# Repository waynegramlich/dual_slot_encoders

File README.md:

# dual_slot_encoders

Quadrature encoder using two slot photointerrupters

## Revision A Issues

* The footprint holes for the slot encoders are too small. [x]

## Revision B Issues

* Use a 2x4 ribbon cable for both encoder signals and motor power.

## Revision D Issues

* Pins 4/5 and 6/7 are swapped in bus_bridge_encoders_sonar (Rev. C)
  and dual_slot_encoders (Rev. D). [Swapped 4/5 and 6/7.]

## Revision E Issuses

* Both resistors are too close to the edge.

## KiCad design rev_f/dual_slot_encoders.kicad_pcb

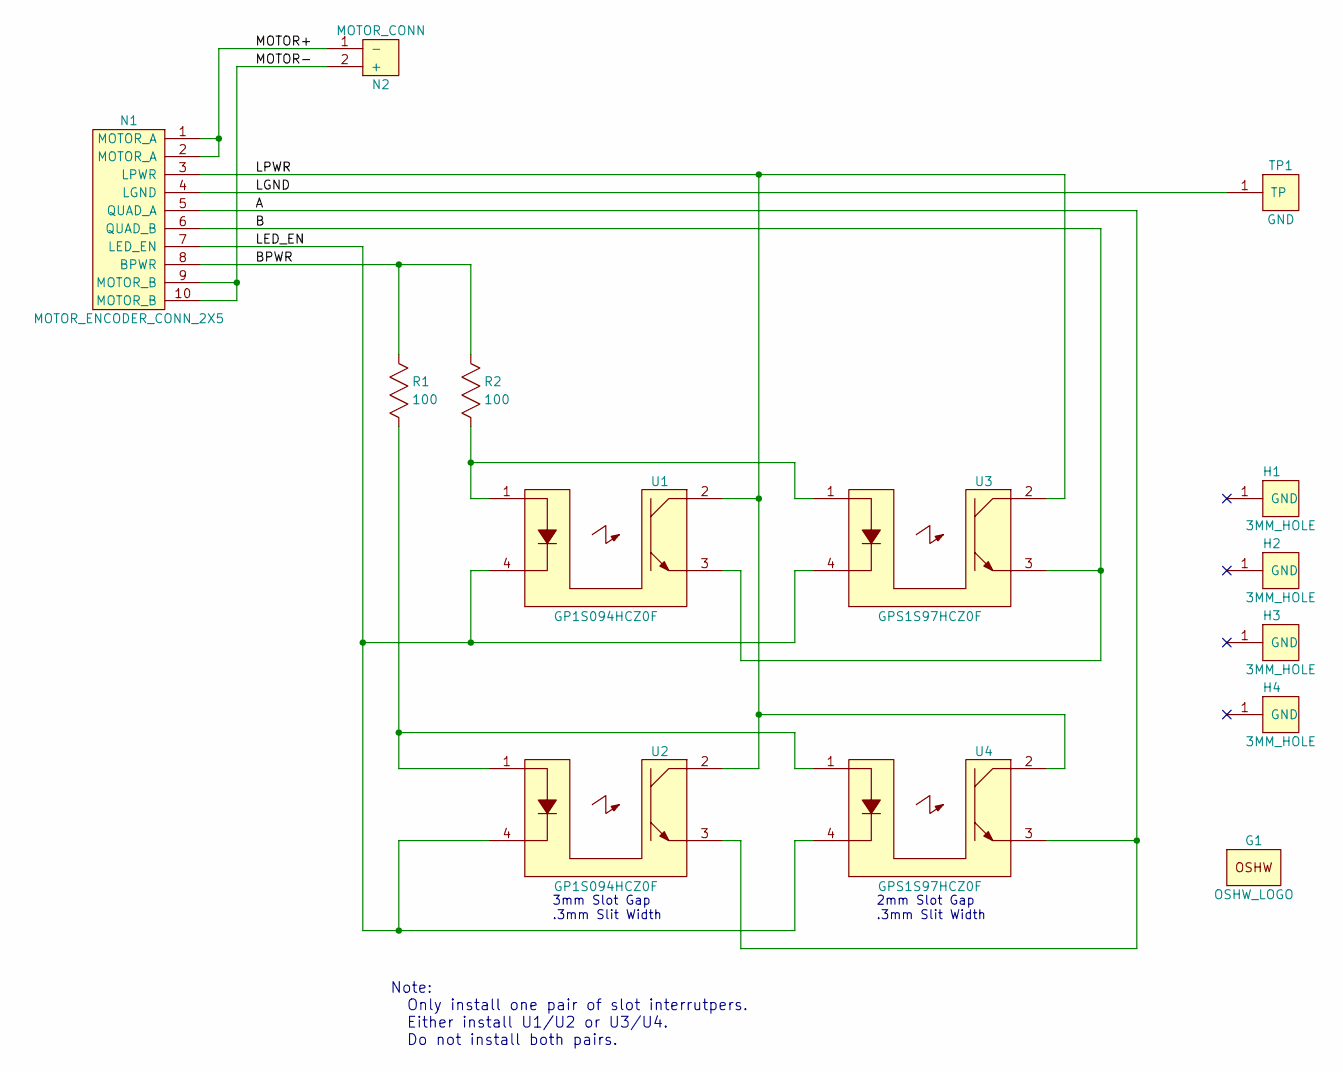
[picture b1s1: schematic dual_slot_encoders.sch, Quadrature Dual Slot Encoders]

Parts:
G1: OSHW_LOGO; OSHW_LOGO_200mil
H1, H2, H3, H4: 3MM_HOLE; MountingHole_3mm
N1: MOTOR_ENCODER_CONN_2X5; Pin_Header_Straight_2x05_Shrouded
N2: MOTOR_CONN; 5MM_TERMINAL_BLOCK_2_POS
R1, R2: 100; Resistor_Horizontal_400
TP1: GND; Pin_Header_Straight_1x01
U1, U2: GP1S094HCZ0F
U3, U4: GPS1S97HCZ0F; GP1S097HCZ0F

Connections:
/A: N1.5 (QUAD_A), U2.3, U4.3
/B: N1.6 (QUAD_B), U1.3, U3.3
/BPWR: N1.8 (BPWR), R1.2, R2.2
/LED_EN: N1.7 (LED_EN), U1.4, U2.4, U3.4, U4.4
/LGND: N1.4 (LGND), TP1.1
/LPWR: N1.3 (LPWR), U1.2, U2.2, U3.2, U4.2
/MOTOR+: N1.1 (MOTOR_A), N1.2 (MOTOR_A), N2.1 (-)
/MOTOR-: N1.9 (MOTOR_B), N1.10 (MOTOR_B), N2.2 (+)
unnamed: R1.1, U2.1, U4.1
unnamed: R2.1, U1.1, U3.1

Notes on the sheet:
3mm Slot Gap .3mm Slit Width
2mm Slot Gap .3mm Slit Width
Note: Only install one pair of slot interrutpers. Either install U1/U2 or U3/U4. Do not install both pairs.

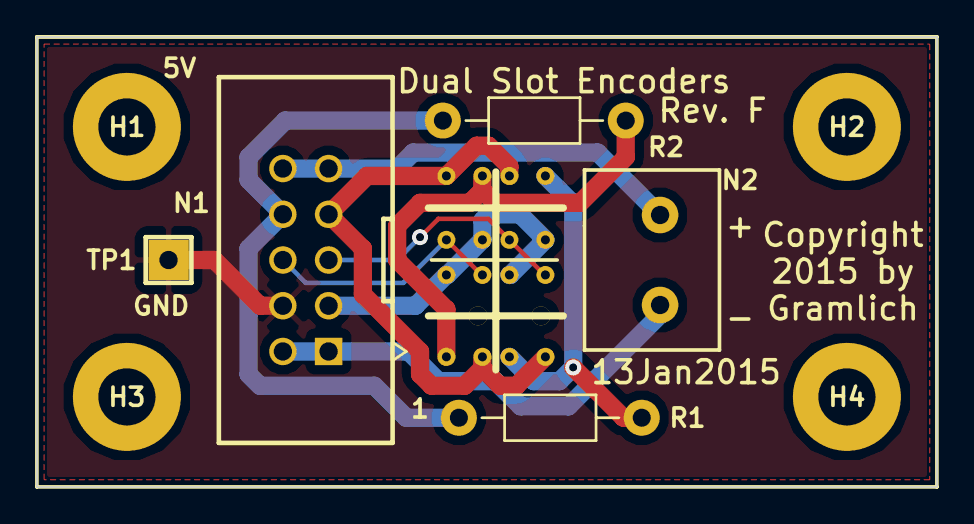
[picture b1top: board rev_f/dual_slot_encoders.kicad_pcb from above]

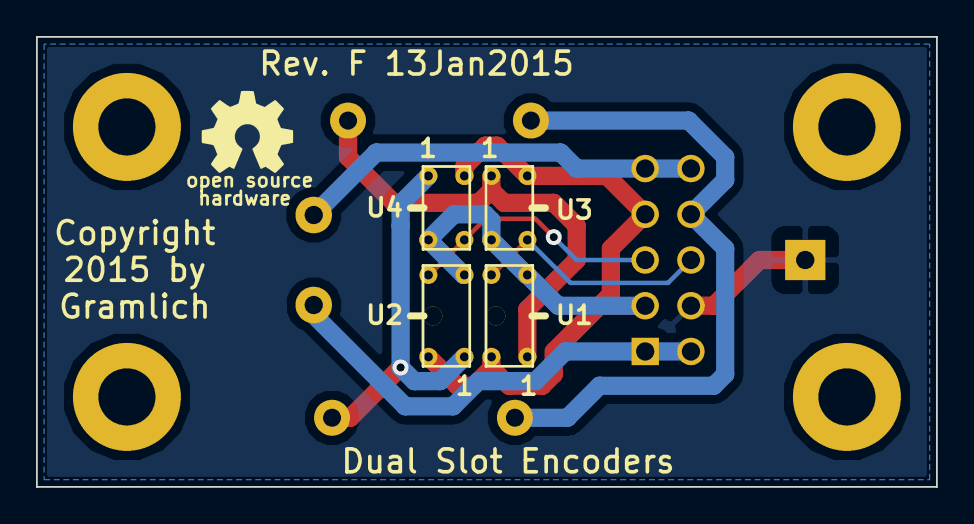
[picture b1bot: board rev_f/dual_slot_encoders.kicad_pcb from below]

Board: 2 copper layers, 50.0 x 25.0 mm, 14 parts (5 on the bottom side), 10 nets.

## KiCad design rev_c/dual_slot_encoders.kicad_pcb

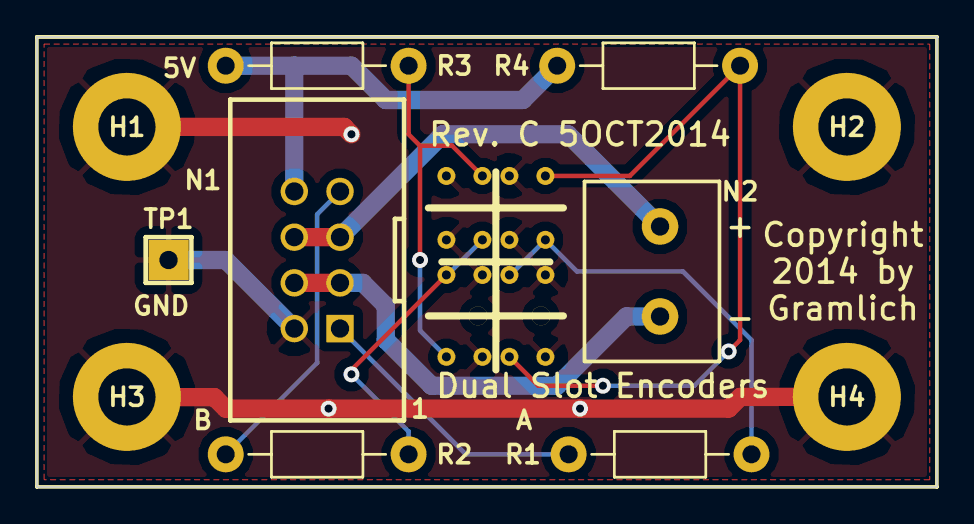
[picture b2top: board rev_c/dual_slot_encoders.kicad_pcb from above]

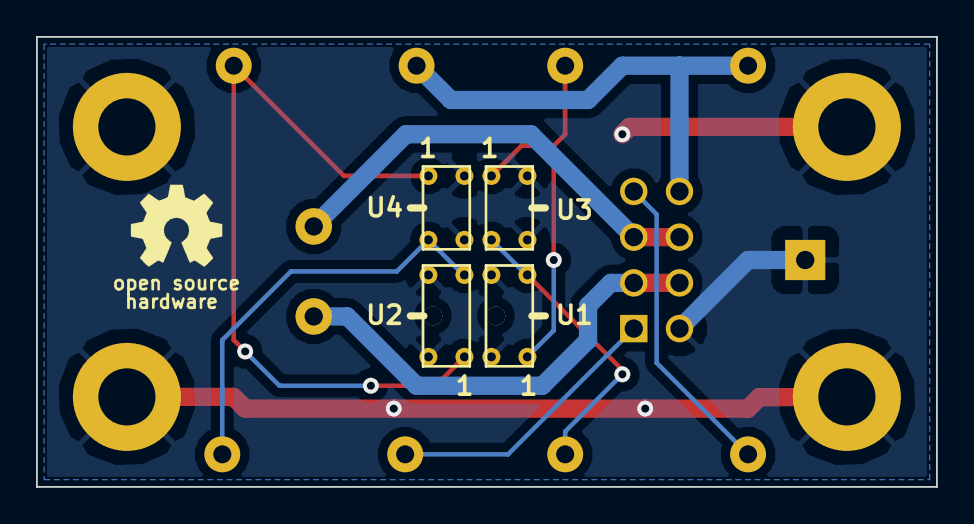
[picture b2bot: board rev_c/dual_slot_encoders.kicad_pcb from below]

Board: 2 copper layers, 50.0 x 25.0 mm, 16 parts (5 on the bottom side), 10 nets.

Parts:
G1: OSHW_LOGO; OSHW_LOGO_200mil
H1, H2, H3, H4: 3MM_HOLE; MountingHole_3mm
N1: MOTOR_ENCODER_CONN; Pin_Header_Straight_2x04_Shrouded
N2: MOTOR_CONN; 5MM_TERMINAL_BLOCK_2_POS
R1, R2: 10K; Resistor_Horizontal_400
R3, R4: 470; Resistor_Horizontal_400
TP1: GND; Pin_Header_Straight_1x01
U1, U2: GP1S094HCZ0F
U3, U4: GPS1S97HCZ0F; GP1S097HCZ0F

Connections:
/5V: N1.8, R3.2, R4.2
/A: N1.1, R1.2
/B: N1.7, R2.2
/GND: H1.1, H2.1, H3.1, H4.1, N1.2, TP1.1, U1.3, U1.4, U2.3, U2.4, U3.3, U3.4, U4.3, U4.4
/MOTOR+: N1.5, N1.6, N2.2
/MOTOR-: N1.3, N1.4, N2.1
unnamed: R1.1, U2.2, U4.2
unnamed: R2.1, U1.2, U3.2
unnamed: R3.1, U1.1, U3.1
unnamed: R4.1, U2.1, U4.1

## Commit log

2014-07-13 Got PCB layed out.
2014-07-13 Added edge cuts.
2014-07-28 Made a clone of Rev. A
2014-07-29 Fixed interrupter lead holes.
2014-10-05 Missed Rev. B .pdf file.
2014-10-05 Updated Rev. A to use fp-lib-table.
2014-10-05 Switch Rev. B to use local fp-lib-table.
2014-10-05 Cloned Rev. C from Rev. B
2014-10-05 Rev. C is pretty much done.
2014-10-11 Rev. C should be done.
2014-10-11 Cloned Rev. C to produce Rev.D
2014-10-11 Rev. D is pretty much ready.
2014-10-28 Removed two stale transistors.
2014-10-30 Clone Rev. D to Rev. E
2014-10-30 Got Rev. E wrapped up.
2015-01-13 Revision F is ready for manufacture.
